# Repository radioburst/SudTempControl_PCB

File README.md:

# SudTempControl_PCB
PCB for SudControl and TempControl2

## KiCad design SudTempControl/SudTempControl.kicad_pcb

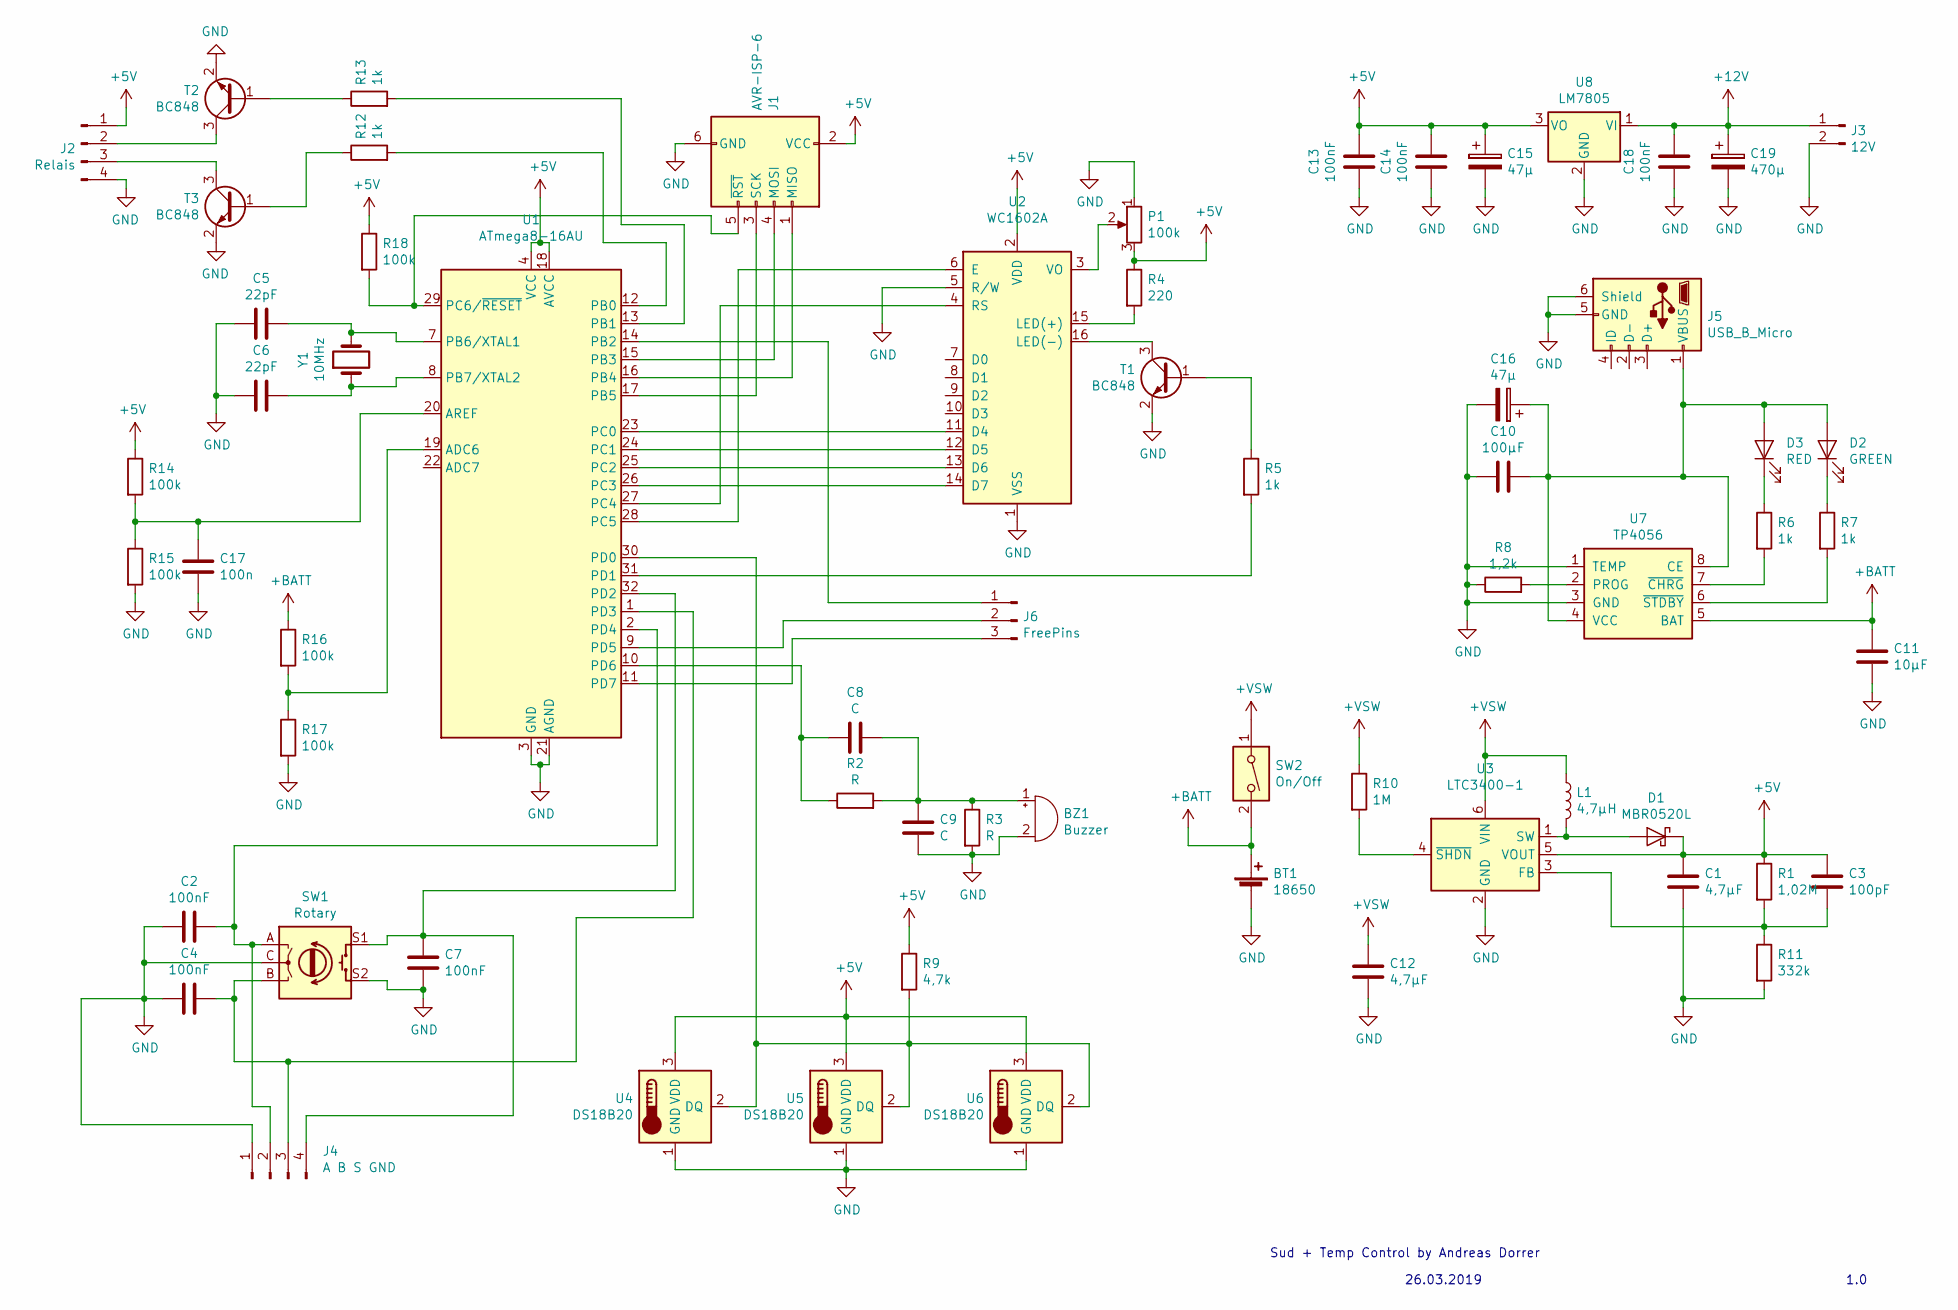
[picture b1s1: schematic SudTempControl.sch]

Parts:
BT1: 18650; BatteryHolder_Keystone_1042_1x18650
BZ1: Buzzer; Buzzer_15x7.5RM7.6
C1, C12: 4,7µF; C_0805_2012Metric_Pad1.15x1.40mm_HandSolder
C2, C4, C7, C13, C14, C18: 100nF; C_0805_2012Metric_Pad1.15x1.40mm_HandSolder
C3: 100pF; C_0805_2012Metric_Pad1.15x1.40mm_HandSolder
C5, C6: 22pF; C_0805_2012Metric_Pad1.15x1.40mm_HandSolder
C8, C9: C; C_0805_2012Metric_Pad1.15x1.40mm_HandSolder
C10: 100µF; C_0805_2012Metric_Pad1.15x1.40mm_HandSolder
C11: 10µF; C_0805_2012Metric_Pad1.15x1.40mm_HandSolder
C15, C16: 47µ; CP_Elec_5x5.4
C17: 100n; C_0805_2012Metric_Pad1.15x1.40mm_HandSolder
C19: 470µ; CP_Elec_5x5.4
D1: MBR0520L; D_SOD-123
D2: GREEN; LED_D3.0mm
D3: RED; LED_D3.0mm
J1: AVR-ISP-6; PinHeader_2x03_P2.54mm_Vertical
J2: Relais; TerminalBlock_Phoenix_MKDS-1,5-4-5.08_1x04_P5.08mm_Horizont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
J3: 12V; PinHeader_1x02_P2.54mm_Vertical
J4: A B S GND; PinHeader_1x04_P2.54mm_Vertical
J5: USB_B_Micro; USB_Micro-B_Wuerth_629105150521
J6: FreePins; PinHeader_1x03_P2.54mm_Vertical
L1: 4,7µH; L_Wuerth_WE-PD2-Typ-L
P1: 100k; Potentiometer_ACP_CA6-VSMD_Vertical
R1: 1,02M; R_0805_2012Metric_Pad1.15x1.40mm_HandSolder
R2, R3: R; R_0805_2012Metric_Pad1.15x1.40mm_HandSolder
R4: 220; R_0805_2012Metric_Pad1.15x1.40mm_HandSolder
R5, R6, R7, R12, R13: 1k; R_0805_2012Metric_Pad1.15x1.40mm_HandSolder
R8: 1,2k; R_0805_2012Metric_Pad1.15x1.40mm_HandSolder
R9: 4,7k; R_0805_2012Metric_Pad1.15x1.40mm_HandSolder
R10: 1M; R_0805_2012Metric_Pad1.15x1.40mm_HandSolder
R11: 332k; R_0805_2012Metric_Pad1.15x1.40mm_HandSolder
R14, R15, R16, R17, R18: 100k; R_0805_2012Metric_Pad1.15x1.40mm_HandSolder
SW1: Rotary; RotaryEncoder_Alps_EC11E-Switch_Vertical_H20mm
SW2: On/Off; SW_SPDT_PCM12
T1, T2, T3: BC848; TSOT-23
U1: ATmega8-16AU; TQFP-32_7x7mm_P0.8mm
U2: WC1602A
U3: LTC3400-1; TSOT-23-6
U4, U5, U6: DS18B20; RJ12_Amphenol_54601
U7: TP4056; SSOP-8_3.95x5.21x3.27mm_P1.27mm
U8: LM7805; TO-252-2
Y1: 10MHz; Crystal_HC18-U_Vertical

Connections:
+5V: C1.1, C3.1, C13.2, C14.2, C15.1, D1.1 (K), J1.2 (VCC), J2.1, P1.3, R1.1, R4.1, R9.1, R14.1, R18.1, U1.4 (VCC), U1.6 (VCC), U1.18 (AVCC), U2.2 (VDD), U3.5 (VOUT), U4.3 (VDD), U5.3 (VDD), U6.3 (VDD), U8.3 (VO)
+12V: C18.2, C19.1, J3.1, U8.1 (VI)
+BATT: BT1.1 (+), C11.2, R16.1, SW2.2, U7.5 (BAT)
+VSW: C12.1, L1.1, R10.1, SW2.1, U3.6 (VIN)
GND: BT1.2 (-), BZ1.2 (+), C1.2, C2.1, C4.1, C5.1, C6.2, C7.1, C9.2, C10.1, C11.1, C12.2, C13.1, C14.1, C15.2, C16.2, C17.2, C18.1, C19.2, J1.6 (GND), J2.4, J3.2, J4.1, J5.5 (GND), J5.6 (Shield), P1.1, R3.2, R8.1, R11.2, R15.2, R17.2, SW1.C, SW1.S2, T1.2 (E), T2.2 (E), T3.2 (E), U1.3 (GND), U1.5 (GND), U1.21 (AGND), U2.1 (VSS), U2.5 (R/W), U3.2 (GND), U4.1 (GND), U5.1 (GND), U6.1 (GND), U7.1 (TEMP), U7.3 (GND), U8.2 (GND)
unnamed: BZ1.1 (-), C8.2, C9.1, R2.2, R3.1
unnamed: C2.2, J4.2, SW1.A, U1.2 (PD4)
unnamed: C3.2, R1.2, R11.1, U3.3 (FB)
unnamed: C4.2, J4.3, SW1.B, U1.1 (PD3)
unnamed: C5.2, U1.7 (PB6/XTAL1), Y1.2
unnamed: C6.1, U1.8 (PB7/XTAL2), Y1.1
unnamed: C7.2, J4.4, SW1.S1, U1.32 (PD2)
unnamed: C8.1, R2.1, U1.10 (PD6)
unnamed: C10.2, C16.1, D2.2 (A), D3.2 (A), J5.1 (VBUS), U7.4 (VCC), U7.8 (CE)
unnamed: C17.1, R14.2, R15.1, U1.20 (AREF)
unnamed: D1.2 (A), L1.2, U3.1 (SW)
unnamed: D2.1 (K), R7.1
unnamed: D3.1 (K), R6.1
unnamed: J1.1 (MISO), U1.16 (PB4)
unnamed: J1.3 (SCK), U1.17 (PB5)
unnamed: J1.4 (MOSI), U1.15 (PB3)
unnamed: J1.5 (~RST), R18.2, U1.29 (PC6/~RESET)
unnamed: J2.2, T2.3 (C)
unnamed: J2.3, T3.3 (C)
unnamed: J6.1, U1.14 (PB2)
unnamed: J6.2, U1.9 (PD5)
unnamed: J6.3, U1.11 (PD7)
unnamed: P1.2, U2.3 (VO)
unnamed: R4.2, U2.15 (LED(+))
unnamed: R5.1, T1.1 (B)
unnamed: R5.2, U1.31 (PD1)
unnamed: R6.2, U7.7 (~CHRG)
unnamed: R7.2, U7.6 (~STDBY)
unnamed: R8.2, U7.2 (PROG)
unnamed: R9.2, U1.30 (PD0), U4.2 (DQ), U5.2 (DQ), U6.2 (DQ)
unnamed: R10.2, U3.4 (~SHDN)
unnamed: R12.1, T3.1 (B)
unnamed: R12.2, U1.12 (PB0)
unnamed: R13.1, T2.1 (B)
unnamed: R13.2, U1.13 (PB1)
unnamed: R16.2, R17.1, U1.19 (ADC6)
unnamed: T1.3 (C), U2.16 (LED(-))
unnamed: U1.23 (PC0), U2.11 (D4)
unnamed: U1.24 (PC1), U2.12 (D5)
unnamed: U1.25 (PC2), U2.13 (D6)
unnamed: U1.26 (PC3), U2.14 (D7)
unnamed: U1.27 (PC4), U2.4 (RS)
unnamed: U1.28 (PC5), U2.6 (E)

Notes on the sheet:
26.03.2019
1.0
Sud + Temp Control by Andreas Dorrer

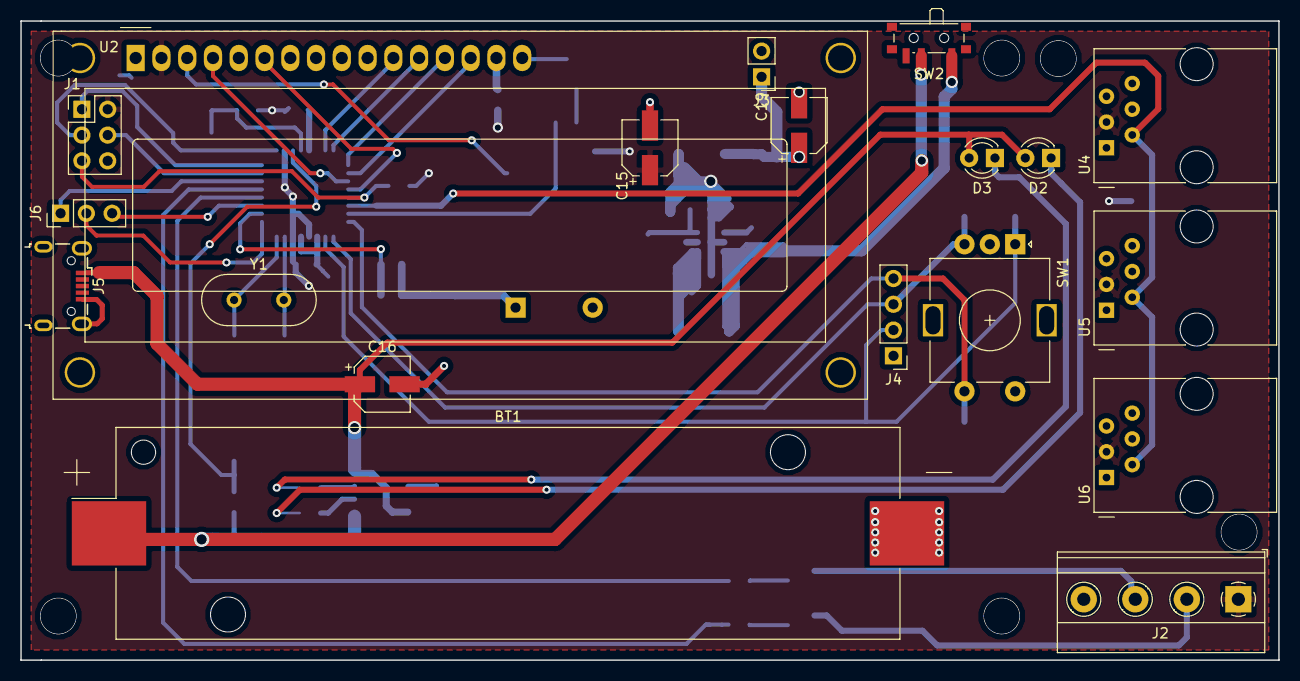
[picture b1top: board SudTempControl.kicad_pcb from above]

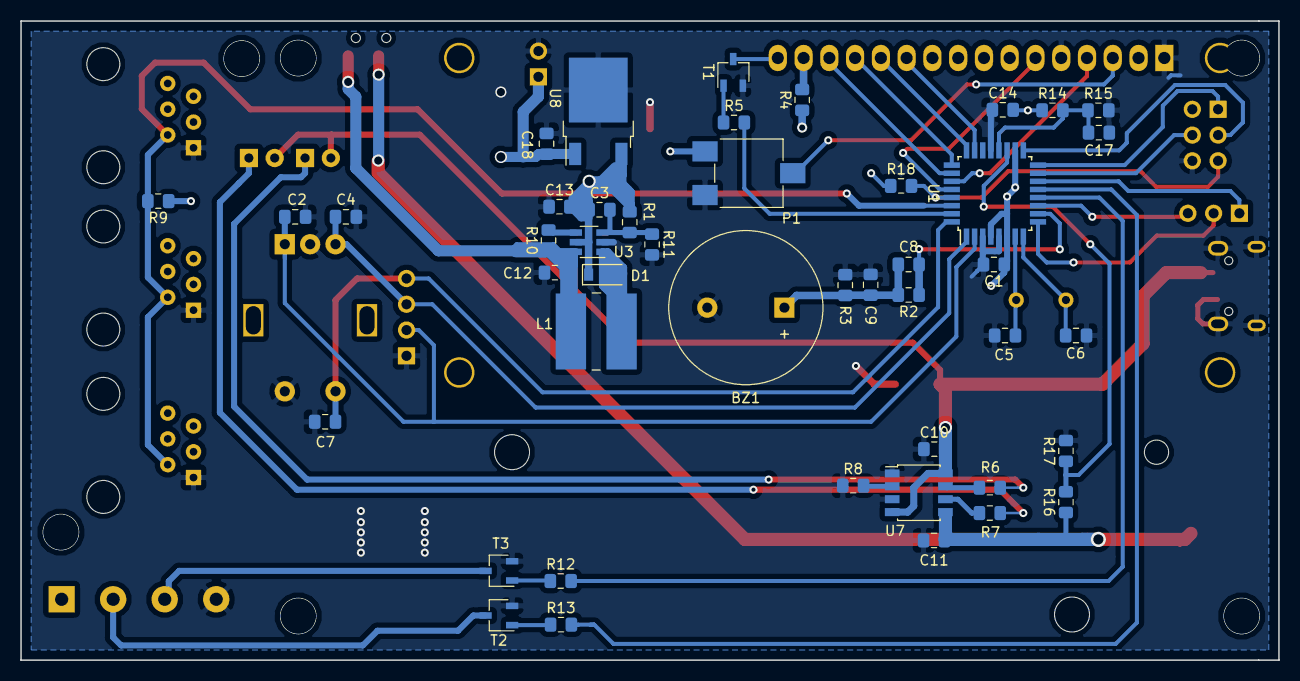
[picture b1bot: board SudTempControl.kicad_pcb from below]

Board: 2 copper layers, 124.0 x 63.0 mm, 64 parts (45 on the bottom side), 48 nets.

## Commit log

2024-04-24 add PCB
